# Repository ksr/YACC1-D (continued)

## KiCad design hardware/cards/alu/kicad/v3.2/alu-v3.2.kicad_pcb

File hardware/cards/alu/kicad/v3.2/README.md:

# alu-v3.2 — KiCad conversion

Generated 2026-09-23 by `tools/eagle_to_kicad_all.py` from the Eagle design `ALU V3.2` in `hardware/cards/alu/eagle/v3.2/`. **The Eagle files are the record of what was designed and built; this KiCad project is derived from them and is regenerated from scratch on every run of the tool** (hand edits here will be lost - once a card is edited in KiCad, remove it from the tool's list). This revision was FABRICATED (see `hardware/FABRICATED.md`).

## Files

| File | What it is |
|---|---|
| `alu-v3.2.kicad_pro` | project; OSH Park rules (6 mil track, 5 mil clearance, 10 mil drill, 4 mil annular) |
| `alu-v3.2.kicad_sch` | root sheet; 9 sub-sheet(s) `alu-v3.2-sheetN.kicad_sch` mirror the Eagle sheets |
| `alu-v3.2-eagle.kicad_sym` | project symbol library generated from the Eagle libraries used (units = Eagle gates) |
| `alu-v3.2.kicad_pcb` | the board: 4 copper layers, 86 footprints, 2254 track segments, 321 vias |
| `alu-v3.2-eagle.pretty/` | project footprint library extracted from the imported board |
| `reports/` | ERC (`erc.json`), DRC (`drc.json`), schematic PDF, board renders (`-top.png`, `-bottom.png`), netlist + `netlist-compare.txt` |

## Proof

Schematic-vs-board netlist comparison (`tools/kicad/compare_netlists.py`: every (reference, pad) partition must be identical): **MATCH (162/162 nets)**

```
  same connectivity, different net name: [('-ADD{slash}SUB', '-ADD/SUB'), ('/Sheet 1/AC-LD', 'AC-LD'), ('/Sheet 1/ACI-DATA0', 'ACI-DATA0'), ('/Sheet 1/ACI-DATA1', 'ACI-DATA1'), ('/Sheet 1/ACI-DATA2', 'ACI-DATA2'), ('/Sheet 1/ACI-DATA3', 'ACI-DATA3'), ('/Sheet 1/ACI-DATA4', 'ACI-DATA4'), ('/Sheet 1/ACI-DATA5', 'ACI-DATA5'), ('/Sheet 1/ACI-DATA6', 'ACI-DATA6'), ('/Sheet 1/ACI-DATA7', 'ACI-DATA7'), ('/Sheet 3/-ALU-IO-EN', '-ALU-IO-EN'), ('/Sheet 6/SR-LD', 'SR-LD'), ('/Sheet 6/SRD0', 'SRD0'), ('/Sheet 6/SRD7', 'SRD7'), ('CO{slash}BO', 'CO/BO'), ('C{slash}SHIFT', 'C/SHIFT'), ('Net-(IC1B-O)', 'SUB'), ('Net-(IC1D-O)', 'N$15'), ('Net-(IC1E-I)', 'N$16'), ('Net-(IC4A-O)', 'N$3'), ('Net-(IC6B-I1)', 'N$52'), ('Net-(IC6C-I1)', 'N$9'), ('Net-(IC6C-O)', 'N$5'), ('Net-(IC7A-O)', 'N$7'), ('Net-(IC14A-O)', 'N$94'), ('Net-(IC14B-O)', 'N$95'), ('Net-(IC14C-O)', 'N$96'), ('Net-(IC14D-O)', 'N$97'), ('Net-(IC15A-O)', 'N$99'), ('Net-(IC15B-O)', 'N$100'), ('Net-(IC15C-O)', 'N$101'), ('Net-(IC15D-O)', 'N$98'), ('Net-(IC18A-O)', 'N$86'), ('Net-(IC18B-O)', 'N$87'), ('Net-(IC18C-O)', 'N$88'), ('Net-(IC18D-O)', 'N$89'), ('Net-(IC19A-O)', 'N$91'), ('Net-(IC19B-O)', 'N$92'), ('Net-(IC19C-O)', 'N$93'), ('Net-(IC19D-O)', 'N$90'), ('Net-(IC21A-O)', 'N$77'), ('Net-(IC21B-O)', 'N$78'), ('Net-(IC21C-O)', 'N$79'), ('Net-(IC21D-O)', 'N$81'), ('Net-(IC22A-O)', 'N$82'), ('Net-(IC22B-O)', 'N$83'), ('Net-(IC22C-O)', 'N$84'), ('Net-(IC22D-O)', 'N$85'), ('Net-(IC24-A<B_O)', 'N$46'), ('Net-(IC24-A=B_O)', 'N$45'), ('Net-(IC24-A>B_O)', 'N$43'), ('Net-(IC25-A<B_O)', 'N$47'), ('Net-(IC25-A=B_O)', 'N$48'), ('Net-(IC25-A>B_O)', 'N$49'), ('Net-(IC26-D4)', 'N$6'), ('Net-(IC26-D6)', 'N$55'), ('Net-(IC26-G)', 'N$4'), ('Net-(IC26-Y)', 'N$56'), ('Net-(IC27A-I0)', 'N$8'), ('Net-(IC27A-O)', 'N$2'), ('Net-(IC27B-I0)', 'N$1'), ('Net-(IC27B-O)', 'N$10'), ('Net-(IC28-1Y)', 'N$75'), ('Net-(IC28-2Y)', 'N$76'), ('Net-(IC29-QB)', 'N$66'), ('Net-(IC29-QC)', 'N$69'), ('Net-(IC29-QD)', 'N$70'), ('Net-(IC30-QA)', 'N$71'), ('Net-(IC30-QB)', 'N$72'), ('Net-(IC30-QC)', 'N$73'), ('Net-(IC32-1Y)', 'N$11'), ('Net-(IC33A-O)', 'N$28'), ('Net-(IC33B-O)', 'N$12'), ('Net-(IC33C-O)', 'N$26'), ('Net-(IC33D-O)', 'N$27'), ('Net-(IC34A-O)', 'N$29'), ('Net-(IC34B-O)', 'N$13'), ('Net-(IC34C-O)', 'N$31'), ('Net-(IC34D-O)', 'N$32'), ('Net-(IC35-C4)', 'N$41'), ('Net-(IC35-S1)', 'N$33'), ('Net-(IC35-S2)', 'N$34'), ('Net-(IC35-S3)', 'N$35'), ('Net-(IC35-S4)', 'N$36'), ('Net-(IC36-S1)', 'N$37'), ('Net-(IC36-S2)', 'N$38'), ('Net-(IC36-S3)', 'N$39'), ('Net-(IC36-S4)', 'N$40'), ('Net-(PWR0-PadA)', 'N$14')]
```

## Readability

`tools/kicad/sch_overlaps.py` over every sheet: text over text 16, text over a symbol body 26, text crossed by a line 42, items off the drawing frame or on the title block 0. What is left is mostly the Eagle drawing itself (parts placed that close in Eagle) or KiCad drawing pin numbers centred on short pins.

## Residual ERC / DRC

ERC by type: endpoint_off_grid 90, isolated_pin_label 55, unconnected_wire_endpoint 61.
`isolated_pin_label` = the converter's per-net global labels (cosmetic); `power_pin_not_driven` / unused-unit notes are the same ones KiCad's own Eagle importer leaves. `unconnected_wire_endpoint` / `pin_not_connected` = wire stubs Eagle leaves bare (mostly net wires ending on a bus, which is drawn as graphics here); since 2026-09-23 the converter no longer hangs a label on every such end (that was most of the label clutter), so they show as KiCad warnings.

DRC by type: items_not_allowed 2, lib_footprint_mismatch 1, silk_edge_clearance 4, silk_over_copper 199, silk_overlap 199, text_height 2, track_width 199; unconnected items 0; schematic parity 0.
Silk-over-pad and clearance notes reflect the Eagle design as drawn; unconnected items are Eagle airwires (parts the design left unrouted).

Converter: converted: 279 symbols, 907 wires, 439 labels, 154 junctions, 31 bus lines, 11 no-connects

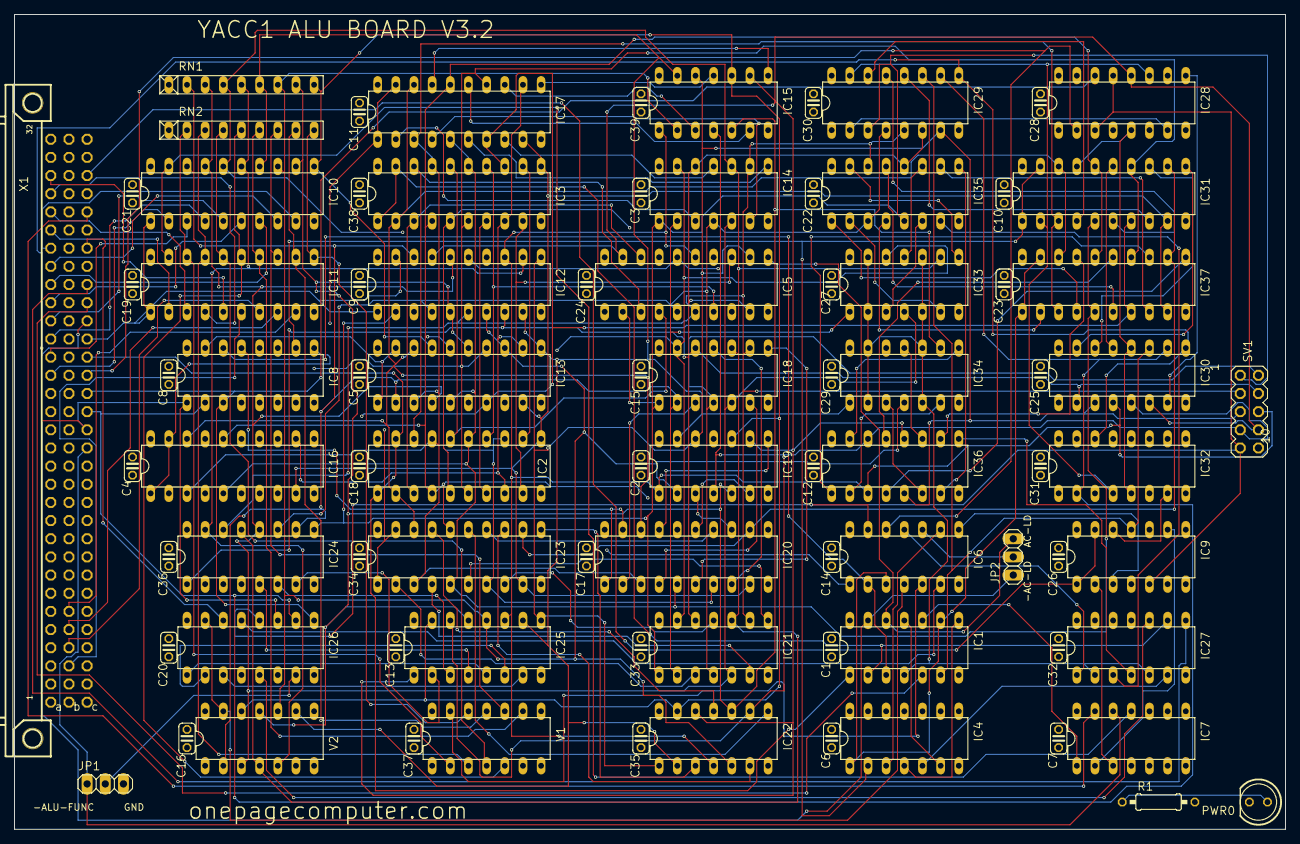
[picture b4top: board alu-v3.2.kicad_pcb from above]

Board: 4 copper layers, 177.8 x 114.0 mm, 86 parts (0 on the bottom side), 162 nets.

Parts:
C1, C2, C3, C4, C5, C6, C7, C8, C9, C10, C11, C12, C13, C14, C15, C16, C17, C18, C19, C20, C22, C23, C24, C25, C26, C27, C28, C29, C30, C31, C32, C33, C34, C35, C36, C37, C38, C39: .1uf; C025-024X044
C21: ,1uf; C025-024X044
IC1: 74ALS04N; DIL14
IC2: 74LS240N; DIL20
IC3, IC12, IC13, IC16, IC17, IC20, IC23, IC31, IC37: 74LS244N; DIL20
IC4: 74LS00N; DIL14
IC5: 74LS374N; DIL20
IC6: 74ALS08N; DIL14
IC7, IC21, IC22: 74LS32N; DIL14
IC8: 74LS138N; DIL16
IC9: 74LS74N; DIL14
IC10, IC11: 74LS245N; DIL20
IC14, IC15, IC27, IC33, IC34: 74LS86N; DIL14
IC18, IC19: 74LS08N; DIL14
IC24, IC25: 74LS85N; DIL16
IC26: 74LS251N; DIL16
IC28, IC32: 74LS153N; DIL16
IC29, IC30: 74LS194N; DIL16
IC35, IC36: 74LS283N; DIL16
JP1, JP2: 1X03
PWR0: LED5MM
R1: 330; 0207_10
RN1, RN2: 10k; RN-9
SV1: MA05-2
V1, V2: 744078N; DIL14
X1: FABC96R

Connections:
-AC-LD: IC1.13, JP2.1, X1.C22
-AC-LD-INV: IC1.1, IC2.1, IC2.19, X1.C20
-AC-RD: IC10.1, IC11.1, IC12.1, IC12.19, X1.C21
-ADD: IC6.1, IC8.7
-ADD/SUB: IC1.9, IC4.1, IC6.3, IC37.1, IC37.19
-ALU-FUNC: IC7.12, JP1.1, X1.C15
-ALU-IO-EN: IC7.11, IC10.19, IC11.19
-AND: IC8.13, IC20.1, IC20.19
-BUS-EN: IC7.13, X1.C28
-DATA: IC8.15, IC13.1, IC13.19
-OR: IC8.12, IC23.1, IC23.19
-RESET: IC9.1, IC9.13, X1.C30
-SHIFT: IC4.2, IC8.10, IC31.1, IC31.19
-SR-LD: IC1.5, X1.C23
-SUB: IC1.3, IC6.2, IC8.14
-XOR: IC8.11, IC17.1, IC17.19
-ZERO: IC8.9, IC16.1, IC16.19
AC-LD: IC1.12, IC5.11, JP2.3
AC-LD-INV: IC1.2, IC3.1, IC3.19, IC27.9
ACI-DATA0: IC2.18, IC3.18, IC5.3
ACI-DATA1: IC2.16, IC3.16, IC5.4
ACI-DATA2: IC2.14, IC3.14, IC5.7
ACI-DATA3: IC2.12, IC3.12, IC5.8
ACI-DATA4: IC2.9, IC3.9, IC5.13
ACI-DATA5: IC2.7, IC3.7, IC5.14
ACI-DATA6: IC2.5, IC3.5, IC5.17
ACI-DATA7: IC2.3, IC3.3, IC5.18
ACO-DATA0: IC5.2, IC12.2, IC14.1, IC18.1, IC21.1, IC24.9, IC29.3, IC35.5, SV1.1
ACO-DATA1: IC5.5, IC12.4, IC14.4, IC18.4, IC21.4, IC24.11, IC29.4, IC35.3, SV1.2
ACO-DATA2: IC5.6, IC12.6, IC14.9, IC18.9, IC21.9, IC24.14, IC29.5, IC35.14, SV1.3
ACO-DATA3: IC5.9, IC12.8, IC14.12, IC18.12, IC21.12, IC24.1, IC29.6, IC30.2, IC35.12, SV1.4
ACO-DATA4: IC5.12, IC12.11, IC15.12, IC19.12, IC22.1, IC25.9, IC29.7, IC30.3, IC36.5, SV1.5
ACO-DATA5: IC5.15, IC12.13, IC15.1, IC19.1, IC22.4, IC25.11, IC30.4, IC36.3, SV1.6
ACO-DATA6: IC5.16, IC12.15, IC15.4, IC19.4, IC22.9, IC25.14, IC30.5, IC36.14, SV1.7
ACO-DATA7: IC5.19, IC12.17, IC15.9, IC19.9, IC22.12, IC25.1, IC28.12, IC30.6, IC36.12, SV1.8
ALU0: IC8.1, IC26.11, IC29.9, IC30.9, IC32.14, X1.C16
ALU1: IC8.2, IC26.10, IC29.10, IC30.10, IC32.2, X1.C17
ALU2: IC8.3, IC26.9, IC28.14, X1.C18
ALU3: IC6.12, IC28.2, X1.C19
BDATA0: IC10.18, IC12.18, IC13.2, IC14.2, IC18.2, IC21.2, IC24.10, IC33.1, RN1.2, V2.2
BDATA1: IC10.17, IC12.16, IC13.4, IC14.5, IC18.5, IC21.5, IC24.12, IC33.4, RN1.3, V2.3
BDATA2: IC10.16, IC12.14, IC13.6, IC14.10, IC18.10, IC21.10, IC24.13, IC33.9, RN1.4, V2.4
BDATA3: IC10.15, IC12.12, IC13.8, IC14.13, IC18.13, IC21.13, IC24.15, IC33.12, RN1.5, V2.5
BDATA4: IC10.14, IC12.9, IC13.11, IC15.13, IC19.13, IC22.2, IC25.10, IC34.1, RN1.6, V2.9
BDATA5: IC10.13, IC12.7, IC13.13, IC15.2, IC19.2, IC22.5, IC25.12, IC34.4, RN1.7, V2.10
BDATA6: IC10.12, IC12.5, IC13.15, IC15.5, IC19.5, IC22.10, IC25.13, IC34.9, RN1.8, V2.11
BDATA7: IC10.11, IC12.3, IC13.17, IC15.10, IC19.10, IC22.13, IC25.15, IC34.12, RN1.9, V2.12
BDATA8: IC11.18, RN2.2, V1.2
BDATA9: IC11.17, RN2.3, V1.3
BDATA10: IC11.16, RN2.4, V1.4
BDATA11: IC11.15, RN2.5, V1.5
BDATA12: IC11.14, RN2.6, V1.9
BDATA13: IC11.13, RN2.7, V1.10
BDATA14: IC11.12, RN2.8, V1.11
BDATA15: IC11.11, RN2.9, V1.12
BR-COND: IC27.8, X1.C24
C/SHIFT: IC6.13, IC9.5, IC26.12, IC28.3, IC28.13, SV1.9
CO/BO: IC1.10, IC7.1
DATA0: IC10.2, X1.A19
DATA1: IC10.3, X1.A20
DATA2: IC10.4, X1.A21
DATA3: IC10.5, X1.A22
DATA4: IC10.6, X1.A23
DATA5: IC10.7, X1.A24
DATA6: IC10.8, X1.A25
DATA7: IC10.9, X1.A26
DATA8: IC11.2, X1.A27
DATA9: IC11.3, X1.A28
DATA10: IC11.4, X1.A29
DATA11: IC11.5, X1.A30
DATA12: IC11.6, X1.B3
DATA13: IC11.7, X1.B4
DATA14: IC11.8, X1.B5
DATA15: IC11.9, X1.B6
GND: C1.2, C2.2, C3.2, C4.2, C5.2, C6.2, C7.2, C8.2, C9.2, C10.2, C11.2, C12.2, C13.2, C14.2, C15.2, C16.2, C17.2, C18.2, C19.2, C20.2, C21.2, C22.2, C23.2, C24.2, C25.2, C26.2, C27.2, C28.2, C29.2, C30.2, C31.2, C32.2, C33.2, C34.2, C35.2, C36.2, C37.2, C38.2, C39.2, IC1.7, IC2.10, IC3.10, IC4.7, IC4.9, IC4.10, IC4.12, IC4.13, IC5.1, IC5.10, IC6.7, IC7.4, IC7.5, IC7.7, IC7.9, IC7.10, IC8.4, IC8.5, IC8.8, IC9.7, IC10.10, IC11.10, IC12.10, IC13.10, IC14.7, IC15.7, IC16.2, IC16.4, IC16.6, IC16.8, IC16.10, IC16.11, IC16.13, IC16.15, IC16.17, IC17.10, IC18.7, IC19.7, IC20.10, IC21.7, IC22.7, IC23.10, IC24.2, IC24.4, IC24.8, IC25.8, IC26.8, IC27.7, IC27.12, IC27.13, IC28.1, IC28.4, IC28.6, IC28.8, IC28.10, IC28.15, IC29.8, IC30.8, IC31.10, IC32.1, IC32.3, IC32.6, IC32.8, IC32.10, IC32.11, IC32.12, IC32.13, IC32.15, IC33.7, IC34.7, IC35.8, IC36.8, IC37.10, JP1.3, PWR0.K, SV1.10, V1.7, V2.7, X1.A1, X1.A32, X1.B1, X1.B32, X1.C1, X1.C32
IN: IC26.14, X1.C26
INV-IN0: IC2.2, IC3.2, IC13.18, IC16.18, IC17.18, IC20.18, IC23.18, IC31.18, IC37.18
INV-IN1: IC2.4, IC3.4, IC13.16, IC16.16, IC17.16, IC20.16, IC23.16, IC31.16, IC37.16
INV-IN2: IC2.6, IC3.6, IC13.14, IC16.14, IC17.14, IC20.14, IC23.14, IC31.14, IC37.14
INV-IN3: IC2.8, IC3.8, IC13.12, IC16.12, IC17.12, IC20.12, IC23.12, IC31.12, IC37.12
INV-IN4: IC2.11, IC3.11, IC13.9, IC16.9, IC17.9, IC20.9, IC23.9, IC31.9, IC37.9
INV-IN5: IC2.13, IC3.13, IC13.7, IC16.7, IC17.7, IC20.7, IC23.7, IC31.7, IC37.7
INV-IN6: IC2.15, IC3.15, IC13.5, IC16.5, IC17.5, IC20.5, IC23.5, IC31.5, IC37.5
INV-IN7: IC2.17, IC3.17, IC13.3, IC16.3, IC17.3, IC20.3, IC23.3, IC31.3, IC37.3
unnamed: IC27.4, IC36.9
unnamed: IC27.3, IC35.7
unnamed: IC4.3, IC6.9
unnamed: IC26.7, JP1.2
unnamed: IC6.8, IC9.3
unnamed: IC6.4, IC26.15, V2.13
unnamed: IC7.3, IC9.2
unnamed: IC6.11, IC27.1
unnamed: IC6.10, JP2.2
unnamed: IC4.5, IC27.6
unnamed: IC9.12, IC32.7
unnamed: IC33.6, IC35.2
unnamed: IC34.6, IC36.2
unnamed: PWR0.A, R1.1
unnamed: IC1.8, IC4.4
unnamed: IC1.11, IC4.6
unnamed: IC33.8, IC35.15
unnamed: IC33.11, IC35.11
unnamed: IC33.3, IC35.6
unnamed: IC34.3, IC36.6
unnamed: IC34.8, IC36.15
unnamed: IC34.11, IC36.11
unnamed: IC35.4, IC37.2
unnamed: IC35.1, IC37.4
unnamed: IC35.13, IC37.6
unnamed: IC35.10, IC37.8
unnamed: IC36.4, IC37.11
unnamed: IC36.1, IC37.13
unnamed: IC36.13, IC37.15
unnamed: IC36.10, IC37.17
unnamed: IC35.9, IC36.7
unnamed: IC24.5, IC25.4
unnamed: IC24.6, IC25.3
unnamed: IC24.7, IC25.2
unnamed: IC25.7, IC26.3
unnamed: IC25.6, IC26.2
unnamed: IC25.5, IC26.1
unnamed: IC6.5, V1.13
unnamed: IC6.6, IC26.13
unnamed: IC26.5, IC27.10
unnamed: IC29.14, IC31.4
unnamed: IC29.13, IC31.6
unnamed: IC29.12, IC31.8
unnamed: IC30.15, IC31.11
unnamed: IC30.14, IC31.13
unnamed: IC30.13, IC31.15
unnamed: IC28.7, IC29.2
unnamed: IC28.9, IC30.7
unnamed: IC21.3, IC23.2
unnamed: IC21.6, IC23.4
unnamed: IC21.8, IC23.6
unnamed: IC21.11, IC23.8
unnamed: IC22.3, IC23.11
unnamed: IC22.6, IC23.13
unnamed: IC22.8, IC23.15
unnamed: IC22.11, IC23.17
unnamed: IC18.3, IC20.2
unnamed: IC18.6, IC20.4
unnamed: IC18.8, IC20.6
unnamed: IC18.11, IC20.8
unnamed: IC19.11, IC20.11
unnamed: IC19.3, IC20.13
unnamed: IC19.6, IC20.15
unnamed: IC19.8, IC20.17
unnamed: IC14.3, IC17.2
unnamed: IC14.6, IC17.4
unnamed: IC14.8, IC17.6
unnamed: IC14.11, IC17.8
unnamed: IC15.11, IC17.11
unnamed: IC15.3, IC17.13
unnamed: IC15.6, IC17.15
unnamed: IC15.8, IC17.17
SHIFT-OUT: IC7.2, IC9.9
SR-LD: IC1.6, IC9.11, IC29.11, IC30.11
SRD0: IC28.11, IC29.15, IC31.2, IC32.4
SRD7: IC28.5, IC30.12, IC31.17, IC32.5
SUB: IC1.4, IC27.2, IC27.5, IC33.2, IC33.5, IC33.10, IC33.13, IC34.2, IC34.5, IC34.10, IC34.13
VCC: C1.1, C2.1, C3.1, C4.1, C5.1, C6.1, C7.1, C8.1, C9.1, C10.1, C11.1, C12.1, C13.1, C14.1, C15.1, C16.1, C17.1, C18.1, C19.1, C20.1, C21.1, C22.1, C23.1, C24.1, C25.1, C26.1, C27.1, C28.1, C29.1, C30.1, C31.1, C32.1, C33.1, C34.1, C35.1, C36.1, C37.1, C38.1, C39.1, IC1.14, IC2.20, IC3.20, IC4.14, IC5.20, IC6.14, IC7.14, IC8.6, IC8.16, IC9.4, IC9.10, IC9.14, IC10.20, IC11.20, IC12.20, IC13.20, IC14.14, IC15.14, IC16.20, IC17.20, IC18.14, IC19.14, IC20.20, IC21.14, IC22.14, IC23.20, IC24.3, IC24.16, IC25.16, IC26.4, IC26.16, IC27.14, IC28.16, IC29.1, IC29.16, IC30.1, IC30.16, IC31.20, IC32.16, IC33.14, IC34.14, IC35.16, IC36.16, IC37.20, R1.2, RN1.1, RN2.1, V1.14, V2.14, X1.A2, X1.A31, X1.B2, X1.B31, X1.C2, X1.C31

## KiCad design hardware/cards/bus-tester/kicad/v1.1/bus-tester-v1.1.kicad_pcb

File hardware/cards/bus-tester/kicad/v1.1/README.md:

# bus-tester-v1.1 — KiCad conversion

Generated 2026-09-23 by `tools/eagle_to_kicad_all.py` from the Eagle design `tester` in `hardware/cards/bus-tester/eagle/v1.1/`. **The Eagle files are the record of what was designed and built; this KiCad project is derived from them and is regenerated from scratch on every run of the tool** (hand edits here will be lost - once a card is edited in KiCad, remove it from the tool's list). This revision was FABRICATED (see `hardware/FABRICATED.md`).

## Files

| File | What it is |
|---|---|
| `bus-tester-v1.1.kicad_pro` | project; OSH Park rules (6 mil track, 5 mil clearance, 10 mil drill, 4 mil annular) |
| `bus-tester-v1.1.kicad_sch` | root sheet; 4 sub-sheet(s) `bus-tester-v1.1-sheetN.kicad_sch` mirror the Eagle sheets |
| `bus-tester-v1.1-eagle.kicad_sym` | project symbol library generated from the Eagle libraries used (units = Eagle gates) |
| `bus-tester-v1.1.kicad_pcb` | the board: 2 copper layers, 86 footprints, 1469 track segments, 173 vias |
| `bus-tester-v1.1-eagle.pretty/` | project footprint library extracted from the imported board |
| `reports/` | ERC (`erc.json`), DRC (`drc.json`), schematic PDF, board renders (`-top.png`, `-bottom.png`), netlist + `netlist-compare.txt` |

## Proof

Schematic-vs-board netlist comparison (`tools/kicad/compare_netlists.py`: every (reference, pad) partition must be identical): **MATCH (149/149 nets)**

```
  same connectivity, different net name: [('/Sheet 3/ARD-RXIN', 'ARD-RXIN'), ('/Sheet 3/ARD-TXOUT', 'ARD-TXOUT'), ('Net-(C10-Pad1)', 'N$9'), ('Net-(IC7-WP)', 'N$2'), ('Net-(IC8-1Q)', 'N$38'), ('Net-(IC8-2Q)', 'N$31'), ('Net-(IC8-3Q)', 'N$35'), ('Net-(IC8-4Q)', 'N$32'), ('Net-(IC8-5Q)', 'N$33'), ('Net-(IC8-6Q)', 'N$34'), ('Net-(IC8-7Q)', 'N$36'), ('Net-(IC8-8Q)', 'N$37'), ('Net-(IC9A-A1)', 'N$40'), ('Net-(IC9A-A2)', 'N$43'), ('Net-(IC9A-A3)', 'N$42'), ('Net-(IC9A-A4)', 'N$41'), ('Net-(IC9B-A1)', 'N$44'), ('Net-(IC9B-A2)', 'N$46'), ('Net-(IC9B-A3)', 'N$47'), ('Net-(IC9B-A4)', 'N$45'), ('Net-(IC10-AREF)', 'N$14'), ('Net-(IC10-PB1(OC1A))', 'N$10'), ('Net-(IC10-PB2(SS{slash}OC1B))', 'N$8'), ('Net-(IC10-PB3(MOSI{slash}OC2))', 'N$7'), ('Net-(IC10-PB4(MISO))', 'N$6'), ('Net-(IC10-PB5(SCK))', 'N$1'), ('Net-(IC10-PB6(XTAL1{slash}TOSC1))', 'N$3'), ('Net-(IC10-PB7(XTAL2{slash}TOSC2))', 'N$4'), ('Net-(IC10-PC0(ADC0))', 'N$18'), ('Net-(IC10-PC1(ADC1))', 'N$19'), ('Net-(IC10-PC2(ADC2))', 'N$39'), ('Net-(JP1-DTR)', 'N$28'), ('Net-(JP1-VCC)', 'N$29'), ('Net-(L0-C)', 'N$26'), ('Net-(L1-C)', 'N$25'), ('Net-(L2-C)', 'N$24'), ('Net-(L3-C)', 'N$23'), ('Net-(L4-C)', 'N$22'), ('Net-(L5-C)', 'N$21'), ('Net-(L6-C)', 'N$20'), ('Net-(L7-C)', 'N$17'), ('Net-(LED1-C)', 'N$12'), ('Net-(LED2-C)', 'N$11'), ('Net-(LED3-C)', 'N$13'), ('Net-(LED4-C)', 'N$15'), ('Net-(LED5-C)', 'N$16'), ('Net-(OUT0-C)', 'N$27'), ('Net-(PWR0-PadA)', 'N$5')]
```

## Readability

`tools/kicad/sch_overlaps.py` over every sheet: text over text 3, text over a symbol body 53, text crossed by a line 22, items off the drawing frame or on the title block 0. What is left is mostly the Eagle drawing itself (parts placed that close in Eagle) or KiCad drawing pin numbers centred on short pins.

## Residual ERC / DRC

ERC by type: endpoint_off_grid 3, unconnected_wire_endpoint 29.
`isolated_pin_label` = the converter's per-net global labels (cosmetic); `power_pin_not_driven` / unused-unit notes are the same ones KiCad's own Eagle importer leaves. `unconnected_wire_endpoint` / `pin_not_connected` = wire stubs Eagle leaves bare (mostly net wires ending on a bus, which is drawn as graphics here); since 2026-09-23 the converter no longer hangs a label on every such end (that was most of the label clutter), so they show as KiCad warnings.

DRC by type: items_not_allowed 2, lib_footprint_mismatch 9, silk_edge_clearance 20, silk_over_copper 199, silk_overlap 11, text_height 8, text_thickness 1; unconnected items 0; schematic parity 0.
Silk-over-pad and clearance notes reflect the Eagle design as drawn; unconnected items are Eagle airwires (parts the design left unrouted).

Converter: converted: 253 symbols, 602 wires, 259 labels, 103 junctions, 5 bus lines, 26 no-connects

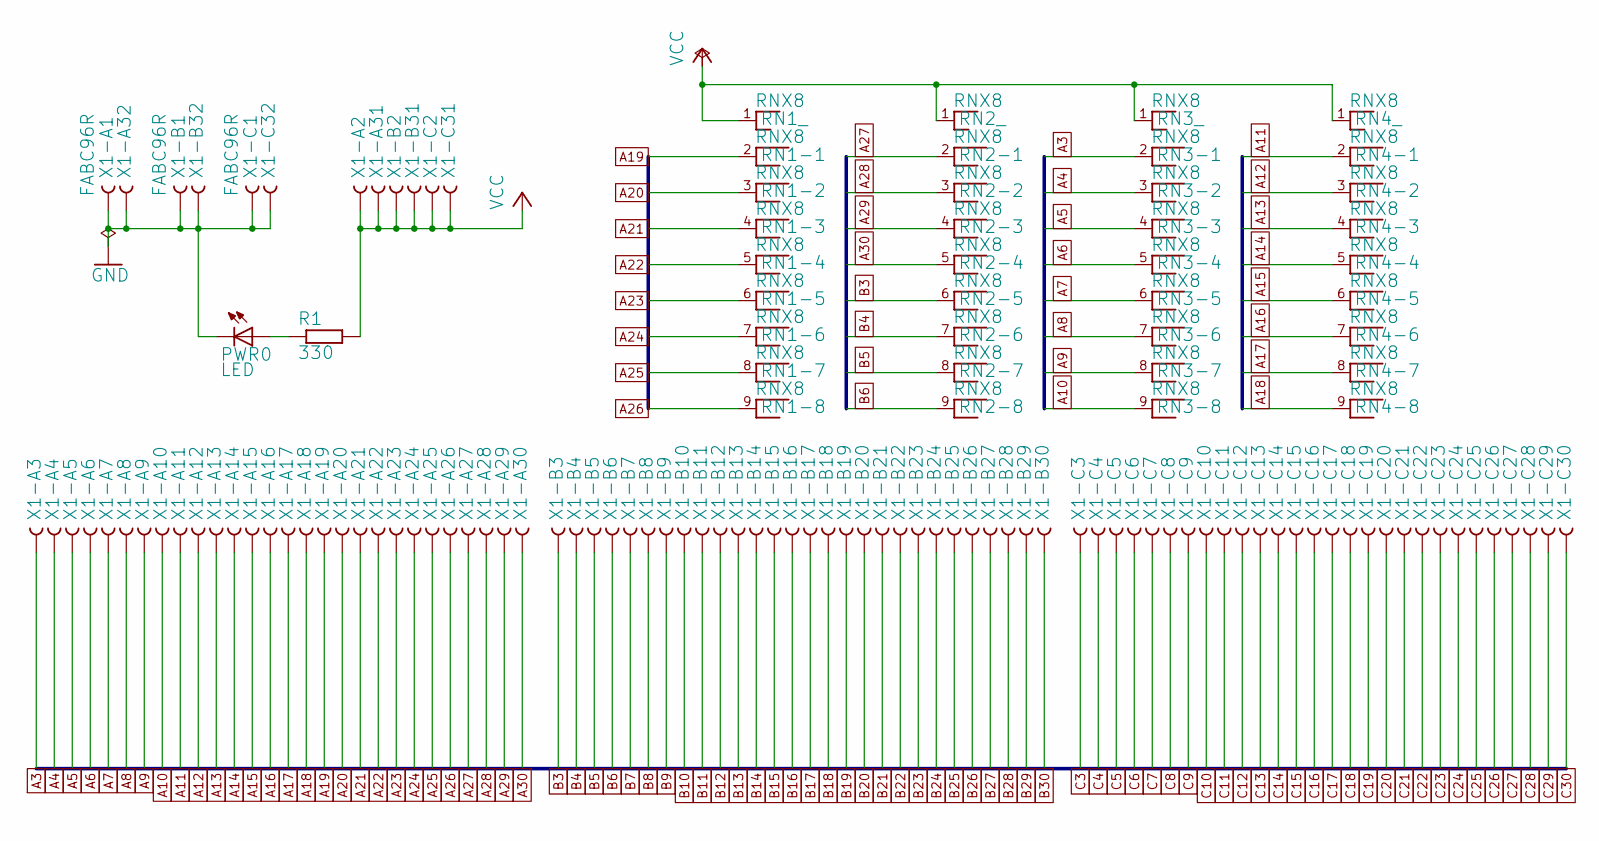
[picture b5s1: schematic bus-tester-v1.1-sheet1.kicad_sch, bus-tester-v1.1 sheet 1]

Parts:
PWR0: LED; LED5MM
R1: 330; 0207_10
RN1, RN2, RN3, RN4: RNX8; RN-9
X1: FABC96R

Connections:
A3: RN3.2, X1.A3; also elsewhere on the board
A4: RN3.3, X1.A4; also elsewhere on the board
A5: RN3.4, X1.A5; also elsewhere on the board
A6: RN3.5, X1.A6; also elsewhere on the board
A7: RN3.6, X1.A7; also elsewhere on the board
A8: RN3.7, X1.A8; also elsewhere on the board
A9: RN3.8, X1.A9; also elsewhere on the board
A10: RN3.9, X1.A10; also elsewhere on the board
A11: RN4.2, X1.A11; also elsewhere on the board
A12: RN4.3, X1.A12; also elsewhere on the board
A13: RN4.4, X1.A13; also elsewhere on the board
A14: RN4.5, X1.A14; also elsewhere on the board
A15: RN4.6, X1.A15; also elsewhere on the board
A16: RN4.7, X1.A16; also elsewhere on the board
A17: RN4.8, X1.A17; also elsewhere on the board
A18: RN4.9, X1.A18; also elsewhere on the board
A19: RN1.2, X1.A19; also elsewhere on the board
A20: RN1.3, X1.A20; also elsewhere on the board
A21: RN1.4, X1.A21; also elsewhere on the board
A22: RN1.5, X1.A22; also elsewhere on the board
A23: RN1.6, X1.A23; also elsewhere on the board
A24: RN1.7, X1.A24; also elsewhere on the board
A25: RN1.8, X1.A25; also elsewhere on the board
A26: RN1.9, X1.A26; also elsewhere on the board
A27: RN2.2, X1.A27; also elsewhere on the board
A28: RN2.3, X1.A28; also elsewhere on the board
A29: RN2.4, X1.A29; also elsewhere on the board
A30: RN2.5, X1.A30; also elsewhere on the board
B3: RN2.6, X1.B3; also elsewhere on the board
B4: RN2.7, X1.B4; also elsewhere on the board
B5: RN2.8, X1.B5; also elsewhere on the board
B6: RN2.9, X1.B6; also elsewhere on the board
B7: X1.B7; also elsewhere on the board
B8: X1.B8; also elsewhere on the board
B9: X1.B9; also elsewhere on the board
B10: X1.B10; also elsewhere on the board
B11: X1.B11; also elsewhere on the board
B12: X1.B12; also elsewhere on the board
B13: X1.B13; also elsewhere on the board
B14: X1.B14; also elsewhere on the board
B15: X1.B15; also elsewhere on the board
B16: X1.B16; also elsewhere on the board
B17: X1.B17; also elsewhere on the board
B18: X1.B18; also elsewhere on the board
B19: X1.B19; also elsewhere on the board
B20: X1.B20; also elsewhere on the board
B21: X1.B21; also elsewhere on the board
B22: X1.B22; also elsewhere on the board
B23: X1.B23; also elsewhere on the board
B24: X1.B24; also elsewhere on the board
B25: X1.B25; also elsewhere on the board
B26: X1.B26; also elsewhere on the board
B27: X1.B27; also elsewhere on the board
B28: X1.B28; also elsewhere on the board
B29: X1.B29; also elsewhere on the board
B30: X1.B30; also elsewhere on the board
C3: X1.C3; also elsewhere on the board
C4: X1.C4; also elsewhere on the board
C5: X1.C5; also elsewhere on the board
C6: X1.C6; also elsewhere on the board
C7: X1.C7; also elsewhere on the board
C8: X1.C8; also elsewhere on the board
C9: X1.C9; also elsewhere on the board
C10: X1.C10; also elsewhere on the board
C11: X1.C11; also elsewhere on the board
C12: X1.C12; also elsewhere on the board
C13: X1.C13; also elsewhere on the board
C14: X1.C14; also elsewhere on the board
C15: X1.C15; also elsewhere on the board
C16: X1.C16; also elsewhere on the board
C17: X1.C17; also elsewhere on the board
C18: X1.C18; also elsewhere on the board
C19: X1.C19; also elsewhere on the board
C20: X1.C20; also elsewhere on the board
C21: X1.C21; also elsewhere on the board
C22: X1.C22; also elsewhere on the board
C23: X1.C23; also elsewhere on the board
C24: X1.C24; also elsewhere on the board
C25: X1.C25; also elsewhere on the board
C26: X1.C26; also elsewhere on the board
C27: X1.C27; also elsewhere on the board
C28: X1.C28; also elsewhere on the board
C29: X1.C29; also elsewhere on the board
C30: X1.C30; also elsewhere on the board
GND: PWR0.K (C), X1.A1, X1.A32, X1.B1, X1.B32, X1.C1, X1.C32; also elsewhere on the board
unnamed: PWR0.A, R1.1
VCC: R1.2, RN1.1, RN2.1, RN3.1, RN4.1, X1.A2, X1.A31, X1.B2, X1.B31, X1.C2, X1.C31; also elsewhere on the board

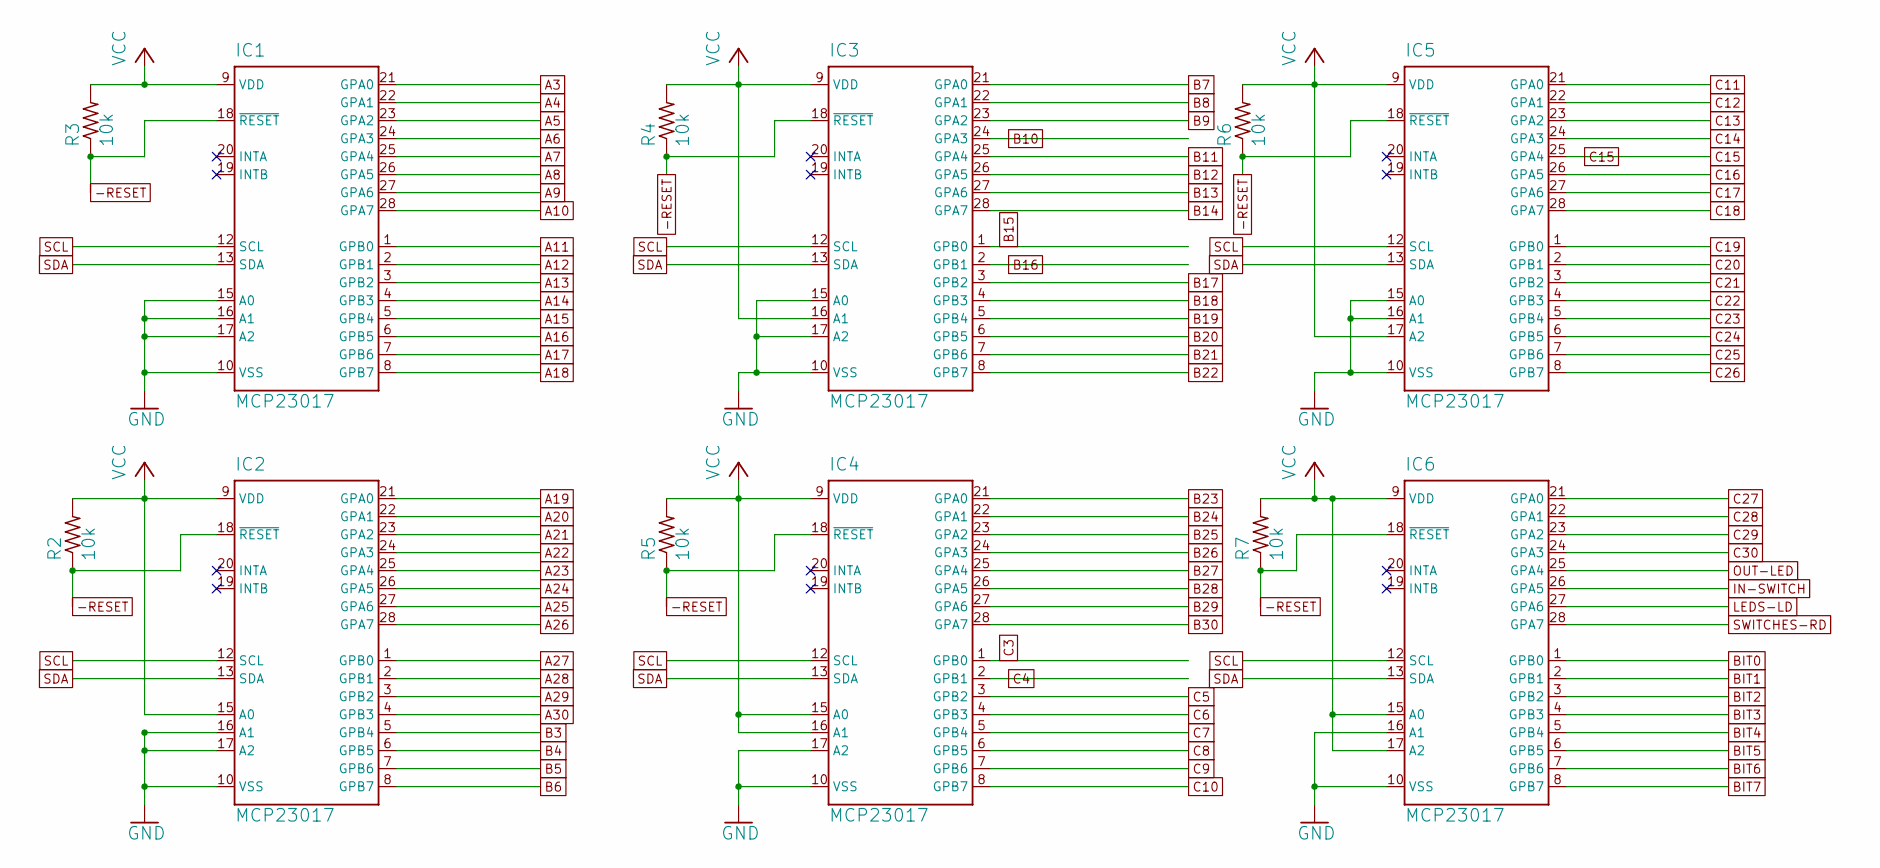
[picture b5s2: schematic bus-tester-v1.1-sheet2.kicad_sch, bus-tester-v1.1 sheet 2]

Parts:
IC1, IC2, IC3, IC4, IC5, IC6: MCP23017; DIL28-3
R2, R3, R4, R5, R6, R7: 10k; 0207_10

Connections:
-RESET: IC1.18 (~RESET), IC2.18 (~RESET), IC3.18 (~RESET), IC4.18 (~RESET), IC5.18 (~RESET), IC6.18 (~RESET), R2.1, R3.1, R4.1, R5.1, R6.1, R7.1; also elsewhere on the board
A3: IC1.21 (GPA0); also elsewhere on the board
A4: IC1.22 (GPA1); also elsewhere on the board
A5: IC1.23 (GPA2); also elsewhere on the board
A6: IC1.24 (GPA3); also elsewhere on the board
A7: IC1.25 (GPA4); also elsewhere on the board
A8: IC1.26 (GPA5); also elsewhere on the board
A9: IC1.27 (GPA6); also elsewhere on the board
A10: IC1.28 (GPA7); also elsewhere on the board
A11: IC1.1 (GPB0); also elsewhere on the board
A12: IC1.2 (GPB1); also elsewhere on the board
A13: IC1.3 (GPB2); also elsewhere on the board
A14: IC1.4 (GPB3); also elsewhere on the board
A15: IC1.5 (GPB4); also elsewhere on the board
A16: IC1.6 (GPB5); also elsewhere on the board
A17: IC1.7 (GPB6); also elsewhere on the board
A18: IC1.8 (GPB7); also elsewhere on the board
A19: IC2.21 (GPA0); also elsewhere on the board
A20: IC2.22 (GPA1); also elsewhere on the board
A21: IC2.23 (GPA2); also elsewhere on the board
A22: IC2.24 (GPA3); also elsewhere on the board
A23: IC2.25 (GPA4); also elsewhere on the board
A24: IC2.26 (GPA5); also elsewhere on the board
A25: IC2.27 (GPA6); also elsewhere on the board
A26: IC2.28 (GPA7); also elsewhere on the board
A27: IC2.1 (GPB0); also elsewhere on the board
A28: IC2.2 (GPB1); also elsewhere on the board
A29: IC2.3 (GPB2); also elsewhere on the board
A30: IC2.4 (GPB3); also elsewhere on the board
B3: IC2.5 (GPB4); also elsewhere on the board
B4: IC2.6 (GPB5); also elsewhere on the board
B5: IC2.7 (GPB6); also elsewhere on the board
B6: IC2.8 (GPB7); also elsewhere on the board
B7: IC3.21 (GPA0); also elsewhere on the board
B8: IC3.22 (GPA1); also elsewhere on the board
B9: IC3.23 (GPA2); also elsewhere on the board
B10: IC3.24 (GPA3); also elsewhere on the board
B11: IC3.25 (GPA4); also elsewhere on the board
B12: IC3.26 (GPA5); also elsewhere on the board
B13: IC3.27 (GPA6); also elsewhere on the board
B14: IC3.28 (GPA7); also elsewhere on the board
B15: IC3.1 (GPB0); also elsewhere on the board
B16: IC3.2 (GPB1); also elsewhere on the board
B17: IC3.3 (GPB2); also elsewhere on the board
B18: IC3.4 (GPB3); also elsewhere on the board
B19: IC3.5 (GPB4); also elsewhere on the board
B20: IC3.6 (GPB5); also elsewhere on the board
B21: IC3.7 (GPB6); also elsewhere on the board
B22: IC3.8 (GPB7); also elsewhere on the board
B23: IC4.21 (GPA0); also elsewhere on the board
B24: IC4.22 (GPA1); also elsewhere on the board
B25: IC4.23 (GPA2); also elsewhere on the board
B26: IC4.24 (GPA3); also elsewhere on the board
B27: IC4.25 (GPA4); also elsewhere on the board
B28: IC4.26 (GPA5); also elsewhere on the board
B29: IC4.27 (GPA6); also elsewhere on the board
B30: IC4.28 (GPA7); also elsewhere on the board
BIT0: IC6.1 (GPB0); also elsewhere on the board
BIT1: IC6.2 (GPB1); also elsewhere on the board
BIT2: IC6.3 (GPB2); also elsewhere on the board
BIT3: IC6.4 (GPB3); also elsewhere on the board
BIT4: IC6.5 (GPB4); also elsewhere on the board
BIT5: IC6.6 (GPB5); also elsewhere on the board
BIT6: IC6.7 (GPB6); also elsewhere on the board
BIT7: IC6.8 (GPB7); also elsewhere on the board
C3: IC4.1 (GPB0); also elsewhere on the board
C4: IC4.2 (GPB1); also elsewhere on the board
C5: IC4.3 (GPB2); also elsewhere on the board
C6: IC4.4 (GPB3); also elsewhere on the board
C7: IC4.5 (GPB4); also elsewhere on the board
C8: IC4.6 (GPB5); also elsewhere on the board
C9: IC4.7 (GPB6); also elsewhere on the board
C10: IC4.8 (GPB7); also elsewhere on the board
C11: IC5.21 (GPA0); also elsewhere on the board
C12: IC5.22 (GPA1); also elsewhere on the board
C13: IC5.23 (GPA2); also elsewhere on the board
C14: IC5.24 (GPA3); also elsewhere on the board
C15: IC5.25 (GPA4); also elsewhere on the board
C16: IC5.26 (GPA5); also elsewhere on the board
C17: IC5.27 (GPA6); also elsewhere on the board
C18: IC5.28 (GPA7); also elsewhere on the board
C19: IC5.1 (GPB0); also elsewhere on the board
C20: IC5.2 (GPB1); also elsewhere on the board
C21: IC5.3 (GPB2); also elsewhere on the board
C22: IC5.4 (GPB3); also elsewhere on the board
C23: IC5.5 (GPB4); also elsewhere on the board
C24: IC5.6 (GPB5); also elsewhere on the board
C25: IC5.7 (GPB6); also elsewhere on the board
C26: IC5.8 (GPB7); also elsewhere on the board
C27: IC6.21 (GPA0); also elsewhere on the board
C28: IC6.22 (GPA1); also elsewhere on the board
C29: IC6.23 (GPA2); also elsewhere on the board
C30: IC6.24 (GPA3); also elsewhere on the board
GND: IC1.10 (VSS), IC1.15 (A0), IC1.16 (A1), IC1.17 (A2), IC2.10 (VSS), IC2.16 (A1), IC2.17 (A2), IC3.10 (VSS), IC3.15 (A0), IC3.17 (A2), IC4.10 (VSS), IC4.17 (A2), IC5.10 (VSS), IC5.15 (A0), IC5.16 (A1), IC6.10 (VSS), IC6.16 (A1); also elsewhere on the board
IN-SWITCH: IC6.26 (GPA5); also elsewhere on the board
LEDS-LD: IC6.27 (GPA6); also elsewhere on the board
OUT-LED: IC6.25 (GPA4); also elsewhere on the board
SCL: IC1.12 (SCL), IC2.12 (SCL), IC3.12 (SCL), IC4.12 (SCL), IC5.12 (SCL), IC6.12 (SCL); also elsewhere on the board
SDA: IC1.13 (SDA), IC2.13 (SDA), IC3.13 (SDA), IC4.13 (SDA), IC5.13 (SDA), IC6.13 (SDA); also elsewhere on the board
SWITCHES-RD: IC6.28 (GPA7); also elsewhere on the board
VCC: IC1.9 (VDD), IC2.9 (VDD), IC2.15 (A0), IC3.9 (VDD), IC3.16 (A1), IC4.9 (VDD), IC4.15 (A0), IC4.16 (A1), IC5.9 (VDD), IC5.17 (A2), IC6.9 (VDD), IC6.15 (A0), IC6.17 (A2), R2.2, R3.2, R4.2, R5.2, R6.2, R7.2; also elsewhere on the board

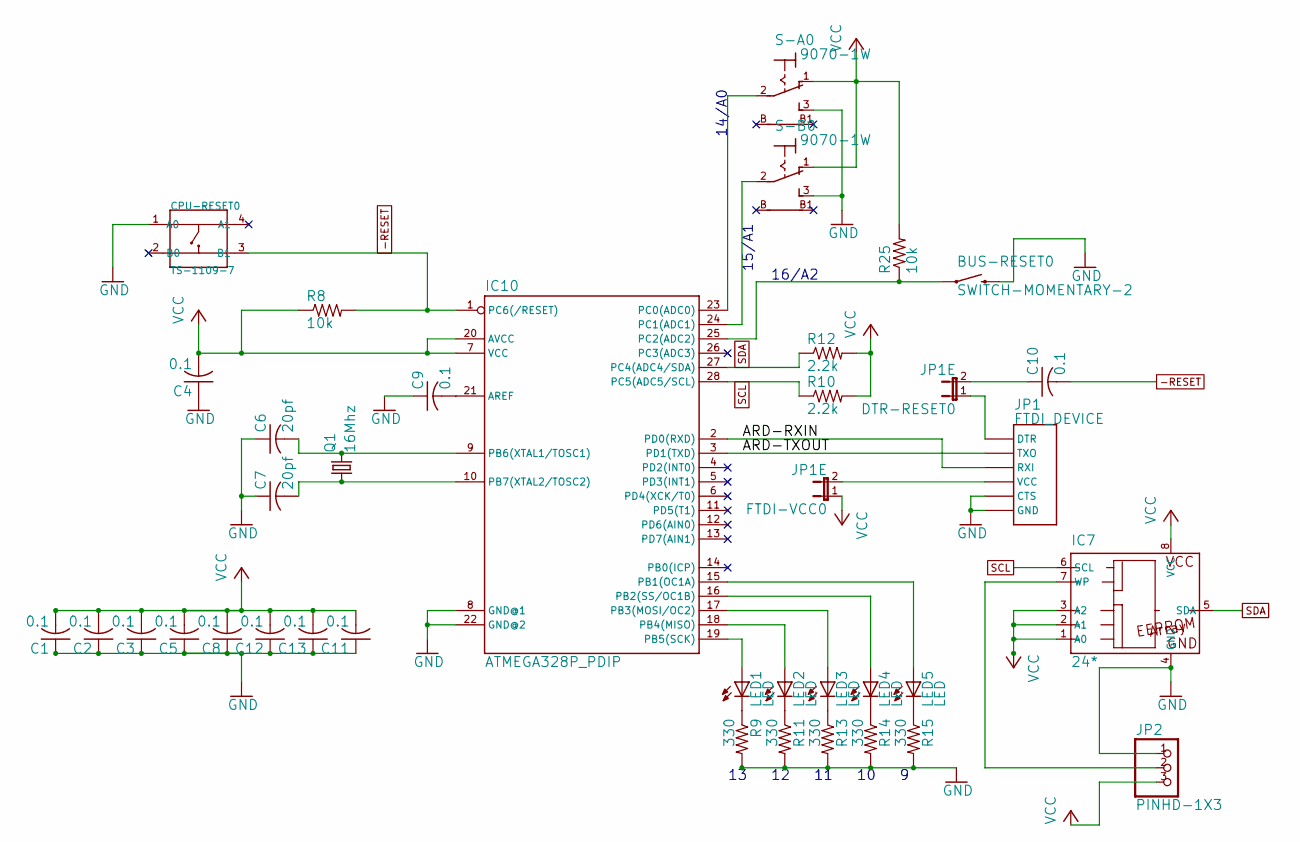
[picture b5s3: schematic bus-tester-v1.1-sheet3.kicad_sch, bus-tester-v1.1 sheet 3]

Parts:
BUS-RESET0: SWITCH-MOMENTARY-2; TACTILE-PTH-SIDEEZ
C1, C2, C3, C4, C5, C8, C9, C10, C11, C12, C13: 0.1; C025-024X044
C6, C7: 20pf; C025-024X044
CPU-RESET0: TS-1109-7; SW4-6.2X6.2X5.0MM
DTR-RESET0: JP1E; JP1
FTDI-VCC0: JP1E; JP1
IC7: 24*; DIL8
IC10: ATMEGA328P_PDIP; DIL28-3
JP1: FTDI_DEVICE; FTDI_DEVICE_SIDE
JP2: PINHD-1X3; 1X03
LED1, LED2, LED3, LED4, LED5: LED; LED5MM
Q1: 16Mhz; HC49_S
R8, R25: 10k; 0207_10
R9, R11, R13, R14, R15: 330; 0207_10
R10, R12: 2.2k; 0207_10
S-A0: 9070-1W
S-B0: 9070-1W

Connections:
-RESET: C10.2, CPU-RESET0.3 (B1), IC10.1 (PC6(/RESET)), R8.2; also elsewhere on the board
ARD-RXIN: IC10.2 (PD0(RXD)), JP1.P$3 (RXI)
ARD-TXOUT: IC10.3 (PD1(TXD)), JP1.P$2 (TXO)
GND: BUS-RESET0.2, C1.1, C2.1, C3.1, C4.1, C5.1, C6.1, C7.1, C8.1, C9.1, C11.1, C12.1, C13.1, CPU-RESET0.1 (A0), IC7.4 (GND), IC10.8 (GND@1), IC10.22 (GND@2), JP1.P$5 (CTS), JP1.P$6 (GND), JP2.1, R9.2, R11.2, R13.2, R14.2, R15.2, S-A0.3 (S), S-B0.3 (S); also elsewhere on the board
unnamed: IC10.19 (PB5(SCK)), LED1.A
unnamed: IC7.7 (WP), JP2.2
unnamed: C6.2, IC10.9 (PB6(XTAL1/TOSC1)), Q1.2
unnamed: C7.2, IC10.10 (PB7(XTAL2/TOSC2)), Q1.1
unnamed: IC10.18 (PB4(MISO)), LED2.A
unnamed: IC10.17 (PB3(MOSI/OC2)), LED3.A
unnamed: IC10.16 (PB2(SS/OC1B)), LED4.A
unnamed: C10.1, DTR-RESET0.2
unnamed: IC10.15 (PB1(OC1A)), LED5.A
unnamed: LED2.K (C), R11.1
unnamed: LED1.K (C), R9.1
unnamed: LED3.K (C), R13.1
unnamed: C9.2, IC10.21 (AREF)
unnamed: LED4.K (C), R14.1
unnamed: LED5.K (C), R15.1
unnamed: IC10.23 (PC0(ADC0)), S-A0.2
unnamed: IC10.24 (PC1(ADC1)), S-B0.2
unnamed: DTR-RESET0.1, JP1.P$1 (DTR)
unnamed: FTDI-VCC0.2, JP1.P$4 (VCC)
unnamed: BUS-RESET0.1, IC10.25 (PC2(ADC2)), R25.1
SCL: IC7.6 (SCL), IC10.28 (PC5(ADC5/SCL)), R10.1; also elsewhere on the board
SDA: IC7.5 (SDA), IC10.27 (PC4(ADC4/SDA)), R12.1; also elsewhere on the board
VCC: C1.2, C2.2, C3.2, C4.2, C5.2, C8.2, C11.2, C12.2, C13.2, FTDI-VCC0.1, IC7.1 (A0), IC7.2 (A1), IC7.3 (A2), IC7.8 (VCC), IC10.7 (VCC), IC10.20 (AVCC), JP2.3, R8.1, R10.2, R12.2, R25.2, S-A0.1 (O), S-B0.1 (O); also elsewhere on the board

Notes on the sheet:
14/A0
15/A1
16/A2

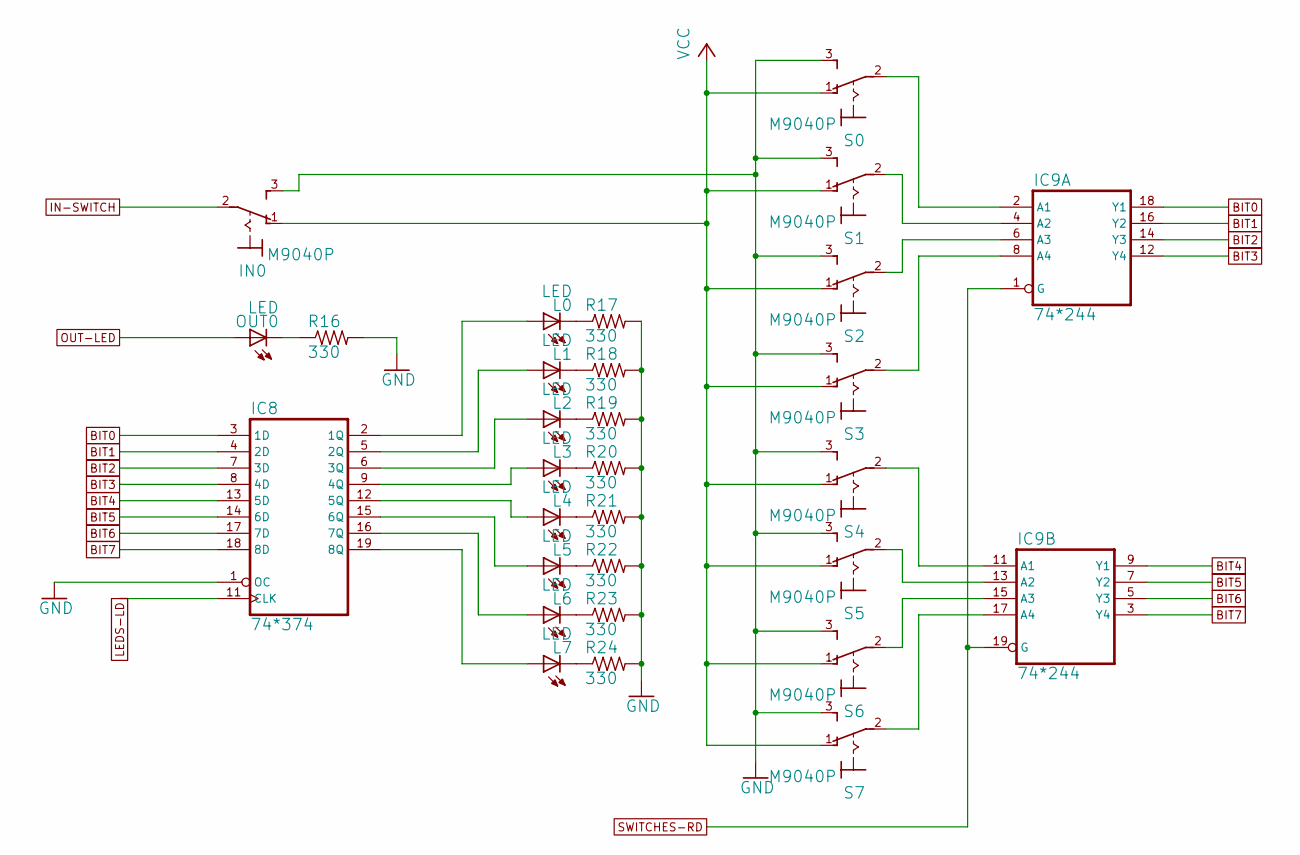
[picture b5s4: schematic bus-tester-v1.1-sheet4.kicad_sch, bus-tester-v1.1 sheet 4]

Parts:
IC8: 74*374; DIL20
IC9: 74*244; DIL20
IN0: M9040P
L0, L1, L2, L3, L4, L5, L6, L7: LED; LED5MM
OUT0: LED; LED5MM
R16, R17, R18, R19, R20, R21, R22, R23, R24: 330; 0207_10
S0, S1, S2, S3, S4, S5, S6, S7: M9040P

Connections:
BIT0: IC8.3 (1D), IC9.18 (Y1); also elsewhere on the board
BIT1: IC8.4 (2D), IC9.16 (Y2); also elsewhere on the board
BIT2: IC8.7 (3D), IC9.14 (Y3); also elsewhere on the board
BIT3: IC8.8 (4D), IC9.12 (Y4); also elsewhere on the board
BIT4: IC8.13 (5D), IC9.9 (Y1); also elsewhere on the board
BIT5: IC8.14 (6D), IC9.7 (Y2); also elsewhere on the board
BIT6: IC8.17 (7D), IC9.5 (Y3); also elsewhere on the board
BIT7: IC8.18 (8D), IC9.3 (Y4); also elsewhere on the board
GND: IC8.1 (OC), IC8.10 (GND), IC9.10 (GND), IN0.3 (S), R16.2, R17.2, R18.2, R19.2, R20.2, R21.2, R22.2, R23.2, R24.2, S0.3 (S), S1.3 (S), S2.3 (S), S3.3 (S), S4.3 (S), S5.3 (S), S6.3 (S), S7.3 (S); also elsewhere on the board
IN-SWITCH: IN0.2; also elsewhere on the board
LEDS-LD: IC8.11 (CLK); also elsewhere on the board
unnamed: L7.K (C), R24.1
unnamed: L6.K (C), R23.1
unnamed: L5.K (C), R22.1
unnamed: L4.K (C), R21.1
unnamed: L3.K (C), R20.1
unnamed: L2.K (C), R19.1
unnamed: L1.K (C), R18.1
unnamed: L0.K (C), R17.1
unnamed: OUT0.K (C), R16.1
unnamed: IC8.5 (2Q), L1.A
unnamed: IC8.9 (4Q), L3.A
unnamed: IC8.12 (5Q), L4.A
unnamed: IC8.15 (6Q), L5.A
unnamed: IC8.6 (3Q), L2.A
unnamed: IC8.16 (7Q), L6.A
unnamed: IC8.19 (8Q), L7.A
unnamed: IC8.2 (1Q), L0.A
unnamed: IC9.2 (A1), S0.2
unnamed: IC9.8 (A4), S3.2
unnamed: IC9.6 (A3), S2.2
unnamed: IC9.4 (A2), S1.2
unnamed: IC9.11 (A1), S4.2
unnamed: IC9.17 (A4), S7.2
unnamed: IC9.13 (A2), S5.2
unnamed: IC9.15 (A3), S6.2
OUT-LED: OUT0.A; also elsewhere on the board
SWITCHES-RD: IC9.1 (G), IC9.19 (G); also elsewhere on the board
VCC: IC8.20 (VCC), IC9.20 (VCC), IN0.1 (O), S0.1 (O), S1.1 (O), S2.1 (O), S3.1 (O), S4.1 (O), S5.1 (O), S6.1 (O), S7.1 (O); also elsewhere on the board
